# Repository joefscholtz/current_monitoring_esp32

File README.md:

# current_monitoring_esp32

Modular firmware project in PlatformIO and hardware design in KiCad using ESP32 and ESP-IDF framework for measuring current and detecting leakage using CT sensors, publishing the data via MQTT through Wifi ( and Ethernet, but not yet fully implemented ). For more informatation on design decisions consult the `docs` directory.

## Project structure

```
.
├── .github/workflows/          # CI/CD
├── app/                        # Two alternatives to consume the library
│   ├── bare_metal/             # Simple Super-Loop implementation
│   └── rtos/                   # RTOS Task-based
├── components/                 # Library ESP-IDF style components
│   └── current_monitor/        # RMS, Differential math, Calibration
│   └── network_manager/        # Wifi, Ethernet and MQTT
├── docs/                       # Documentation
├── kicad/                      # KiCad files
│   └── current_monitor_board/  # KiCad project
│   └── mods/                   # KiCad libraries
├── scripts/                    # Scripts for the project
├── test/                       # Unit tests for the monitor library
├── platformio.ini              # Multi-environment config
├── wokwi.toml                  # Simulation config for ESP32 + Sensors
└── diagram.json                # Wokwi hardware layout
```

## Installation

### With Docker

Requirements:

- Docker
- Docker Compose
- just (Optional)

using just:

```bash
just dev init
```

without just

```bash
DOCKER_COMPOSE_SERVICE=current_monitoring_esp32-app

docker-compose run --rm $DOCKER_COMPOSE_SERVICE just init
```

### Without Docker:

Requirements:

- uv (Python manager)
- PlatformIO CLI
- Wokwi (Optional, needed for simulation)
- just (Optional)

using just:

```bash
just init
```

without just

```bash
uv sync
uv run pio run -t compiledb
```

### Git hooks

using uv and just

```bash
just pre-commit-init
```

using only uv

```bash
uv run pre-commit install --hook-type pre-commit --hook-type pre-push
```

and it can also be installed using only Python.

## Build

### With Docker

using just:

```bash
just dev build
```

without just

```bash
DOCKER_COMPOSE_SERVICE=current_monitoring_esp32-app

docker-compose run --rm $DOCKER_COMPOSE_SERVICE just build
```

### Without Docker:

using just:

```bash
just build
```

without just

```bash
uv run pio run -e bare_metal -e rtos
```

## Flash

...

## TODO

### current_monitor:

- [x] Acquisition interval missed
- [x] Convert raw into voltage
- [x] Calibration
- [ ] Move pin definitions to Kconfig
- [ ] Check `MAX_DIGI_VALUE`

### mqtt:

### App:

### Flash

- [ ] Add flash scripts
- [ ] efuse
- [ ] self-contained flash script

### Docs:

- [x] Hardware mapping
- [x] C4 model

### KiCad

- [ ] MQTT thru Ethernet

### Other:

- [x] Test with PlatformIO IDE
- [ ] Run Tests without `static inline` functions

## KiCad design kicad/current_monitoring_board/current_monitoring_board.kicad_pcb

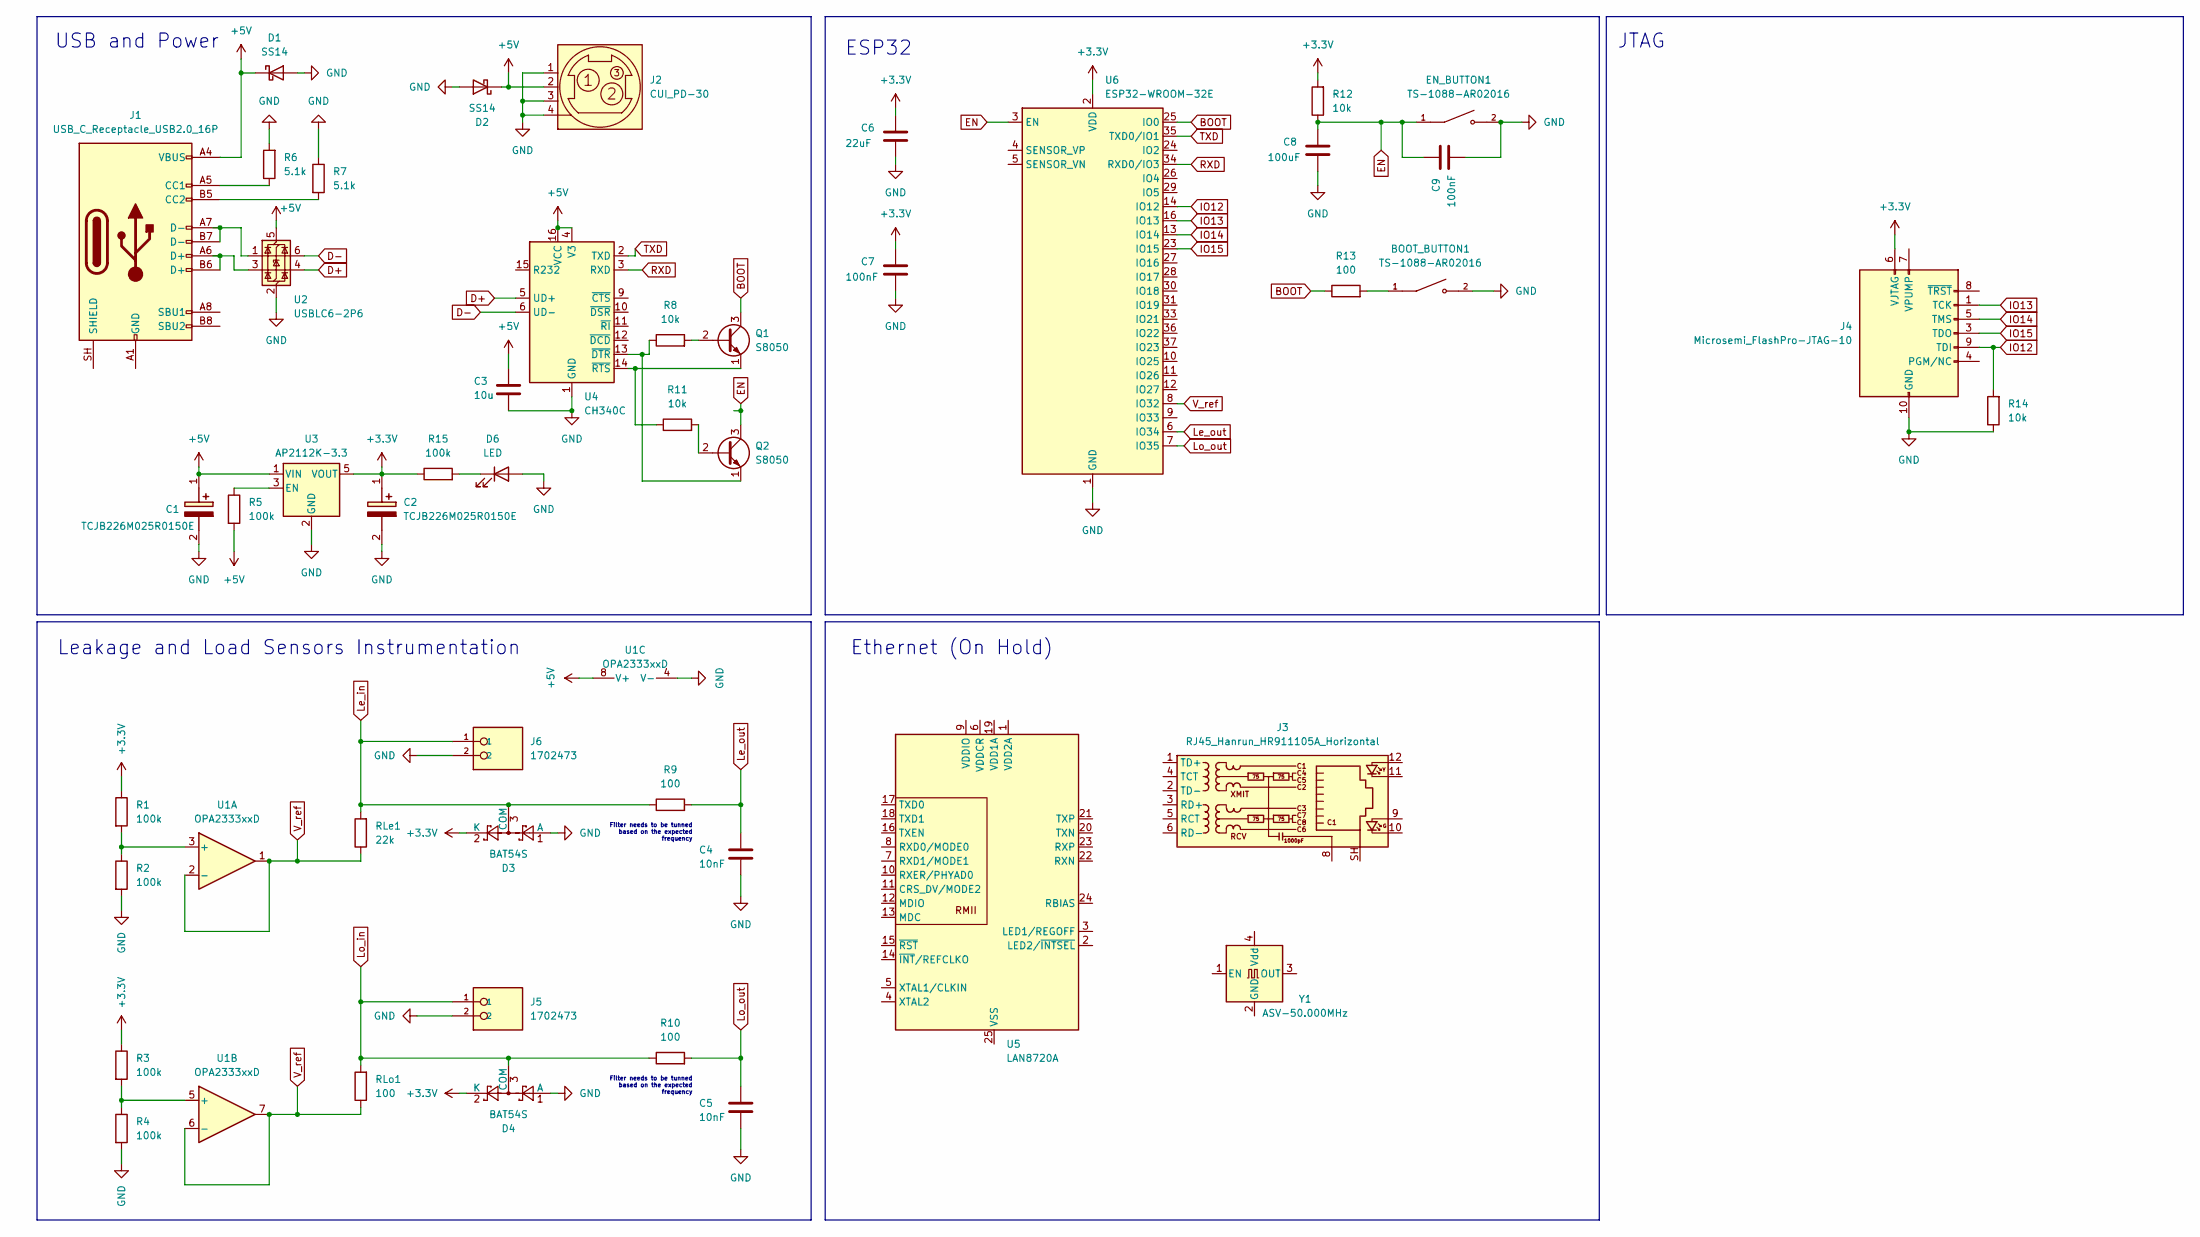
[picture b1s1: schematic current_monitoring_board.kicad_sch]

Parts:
BOOT_BUTTON1: TS-1088-AR02016; SW_SPST_TS-1088-xR020; PARTREV N/A
C1, C2: TCJB226M025R0150E; CP_EIA-1608-08_AVX-J; Mouser Part Number 581-CJB226M025R0150E
C3: 10u; C_0402_1005Metric
C4, C5: 10nF; C_0402_1005Metric
C6: 22uF; C_0402_1005Metric
C7, C9: 100nF; C_0402_1005Metric
C8: 100uF; C_0402_1005Metric
D1, D2: SS14; D_SMA
D3, D4: BAT54S; SOT-23
D6: LED; LED_0402_1005Metric
EN_BUTTON1: TS-1088-AR02016; SW_SPST_TS-1088-xR020; PARTREV N/A
J1: USB_C_Receptacle_USB2.0_16P; USB_C_Receptacle_GCT_USB4105-xx-A_16P_TopMnt_Horizontal
J2: CUI_PD-30
J3: RJ45_Hanrun_HR911105A_Horizontal
J4: Microsemi_FlashPro-JTAG-10; IDC-Header_2x05_P2.54mm_Vertical_SMD
J5, J6: 1702473; PHOENIX_1702473; PARTREV 09.11.2015
Q1, Q2: S8050; TO-92_Inline
R1, R2, R3, R4, R5, R15: 100k; R_0805_2012Metric
R6, R7: 5.1k; R_0805_2012Metric
R8, R11, R12, R14: 10k; R_0805_2012Metric
R9, R10, R13: 100; R_0805_2012Metric
RLe1: 22k; R_0805_2012Metric
RLo1: 100; R_0805_2012Metric
U1: OPA2333xxD; SOIC-8_3.9x4.9mm_P1.27mm
U2: USBLC6-2P6; SOT-666
U3: AP2112K-3.3; SOT-23-5
U4: CH340C; SOIC-16_3.9x9.9mm_P1.27mm
U5: LAN8720A; QFN-24-1EP_4x4mm_P0.5mm_EP2.6x2.6mm
U6: ESP32-WROOM-32E
Y1: ASV-50.000MHz; Oscillator_SMD_Abracon_ASV-4Pin_7.0x5.1mm

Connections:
+3.3V: C2.1 (+), C6.1, C7.1, D3.2 (K), D4.2 (K), J4.6 (VJTAG), R1.1, R3.1, R12.2, R15.1, U3.5 (VOUT), U6.2 (VDD)
+5V: C1.1 (+), C3.1, D1.1 (K), D2.1 (K), J1.A4 (VBUS), J1.A9 (VBUS), J1.B4 (VBUS), J1.B9 (VBUS), J2.2, R5.2, U1.8 (V+), U2.5 (VBUS), U3.1 (VIN), U4.4 (V3), U4.16 (VCC)
BOOT: Q1.3 (C), R13.1, U6.25 (IO0)
D+: U2.4 (I/O2), U4.5 (UD+)
D-: U2.6 (I/O1), U4.6 (UD-)
EN: C8.1, C9.1, EN_BUTTON1.1, Q2.3 (C), R12.1, U6.3 (EN)
GND: BOOT_BUTTON1.2, C1.2 (-), C2.2 (-), C3.2, C4.2, C5.2, C6.2, C7.2, C8.2, C9.2, D1.2 (A), D2.2 (A), D3.1 (A), D4.1 (A), D6.2 (A), EN_BUTTON1.2, J2.1, J2.3, J2.4 (Shield), J4.2 (GND), J4.10 (GND), J5.2, J6.2, R2.2, R4.2, R6.2, R7.1, R14.1, U1.4 (V-), U2.2 (GND), U3.2 (GND), U4.1 (GND), U6.1 (GND), U6.15 (GND), U6.38 (GND), U6.39 (GND)
IO12: J4.9 (TDI), R14.2, U6.14 (IO12)
IO13: J4.1 (TCK), U6.16 (IO13)
IO14: J4.5 (TMS), U6.13 (IO14)
IO15: J4.3 (TDO), U6.23 (IO15)
Le_in: D3.3 (COM), J6.1, R9.1, RLe1.2
Le_out: C4.1, R9.2, U6.6 (IO34)
Lo_in: D4.3 (COM), J5.1, R10.1, RLo1.2
Lo_out: C5.1, R10.2, U6.7 (IO35)
unnamed: BOOT_BUTTON1.1, R13.2
unnamed: D6.1 (K), R15.2
unnamed: J1.A5 (CC1), R6.1
unnamed: J1.B5 (CC2), R7.2
unnamed: J1.A6 (D+), J1.B6 (D+), U2.3 (I/O2)
unnamed: J1.A7 (D-), J1.B7 (D-), U2.1 (I/O1)
unnamed: J1.A1 (GND), J1.A12 (GND), J1.B1 (GND), J1.B12 (GND)
unnamed: Q1.2 (B), R8.2
unnamed: Q1.1 (E), R11.1, U4.14 (~RTS)
unnamed: Q2.2 (B), R11.2
unnamed: Q2.1 (E), R8.1, U4.13 (~DTR)
unnamed: R1.2, R2.1, U1.3 (+)
unnamed: R3.2, R4.1, U1.5 (+)
unnamed: R5.1, U3.3 (EN)
RXD: U4.3 (RXD), U6.34 (RXD0/IO3)
TXD: U4.2 (TXD), U6.35 (TXD0/IO1)
V_ref: RLe1.1, RLo1.1, U1.1, U1.2 (-), U1.6 (-), U1.7, U6.8 (IO32)

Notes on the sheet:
Ethernet (On Hold)
Filter needs to be tunned based on the expected frequency
ESP32
Leakage and Load Sensors Instrumentation
USB and Power
JTAG

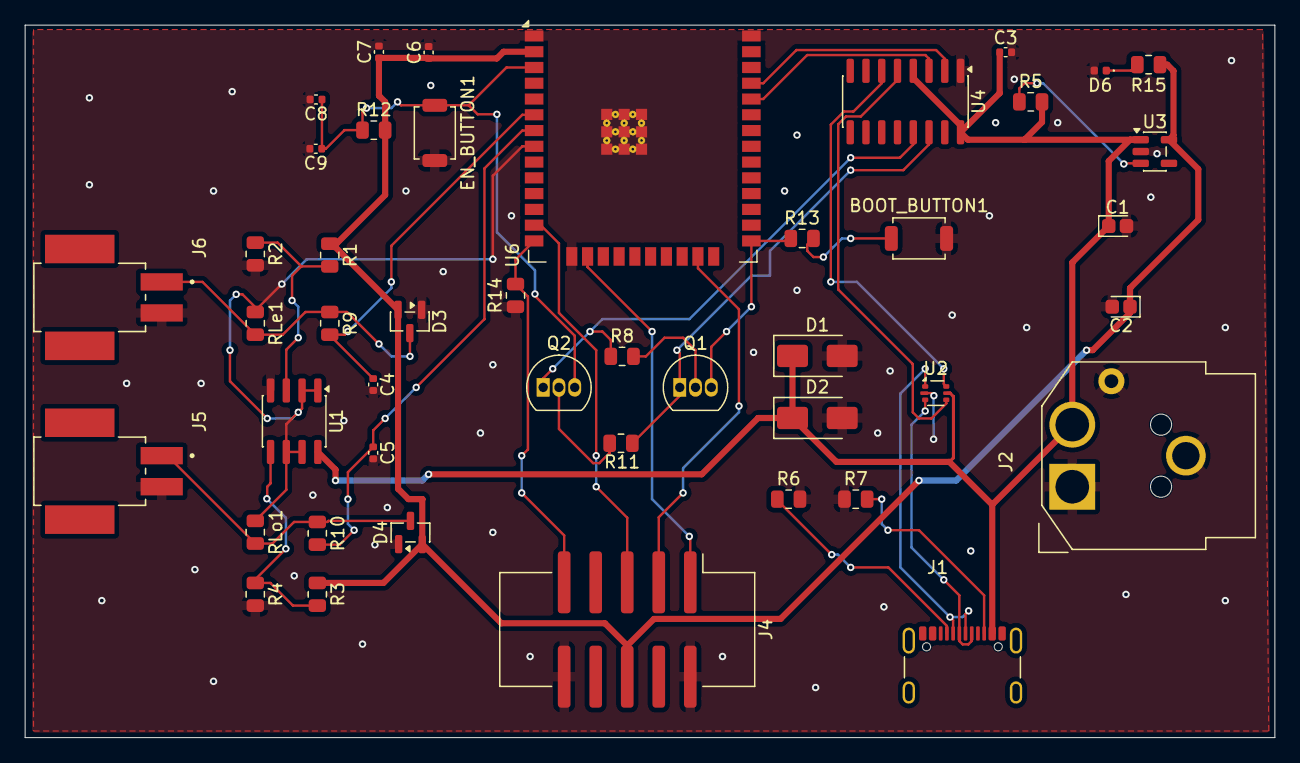
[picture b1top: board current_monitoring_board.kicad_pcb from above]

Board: 2 copper layers, 100.7 x 57.4 mm, 45 parts (0 on the bottom side), 32 nets.

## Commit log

2026-05-07 initialize project structure
2026-05-07 configure project: running
2026-05-08 update justfile
2026-05-08 start versioning kicad files
2026-05-09 first version of pcb
2026-05-12 boilerplate for bare_metal and rtos using current_monitor component
2026-05-12 fix multiple apps configuration
2026-05-12 ci boilerplate
2026-05-12 local ci working
2026-05-12 local ci in different stages
2026-05-12 update build image driver
2026-05-12 add gh ws as safe dir
2026-05-12 gh ws fetch full history
2026-05-12 update README after first current_monitor version
2026-05-12 remove simulate step
2026-05-12 use FROM espressif/idf:v5.2.1
2026-05-12 add network_manager component
2026-05-13 implement network_manager in bare_metal
2026-05-13 network_manager using handlers
2026-05-13 update readme with network_manager
2026-05-13 update board image
2026-05-13 update readme after network_manager
2026-05-13 first version of design doc
2026-05-13 refactor calibration
2026-05-13 fix readme build step
2026-05-13 update vref vias
